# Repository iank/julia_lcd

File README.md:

# julia_lcd

TFT LCD panel, capacitive touch controller, Xilinx Cyclone IV FPGA, SDR SDRAM

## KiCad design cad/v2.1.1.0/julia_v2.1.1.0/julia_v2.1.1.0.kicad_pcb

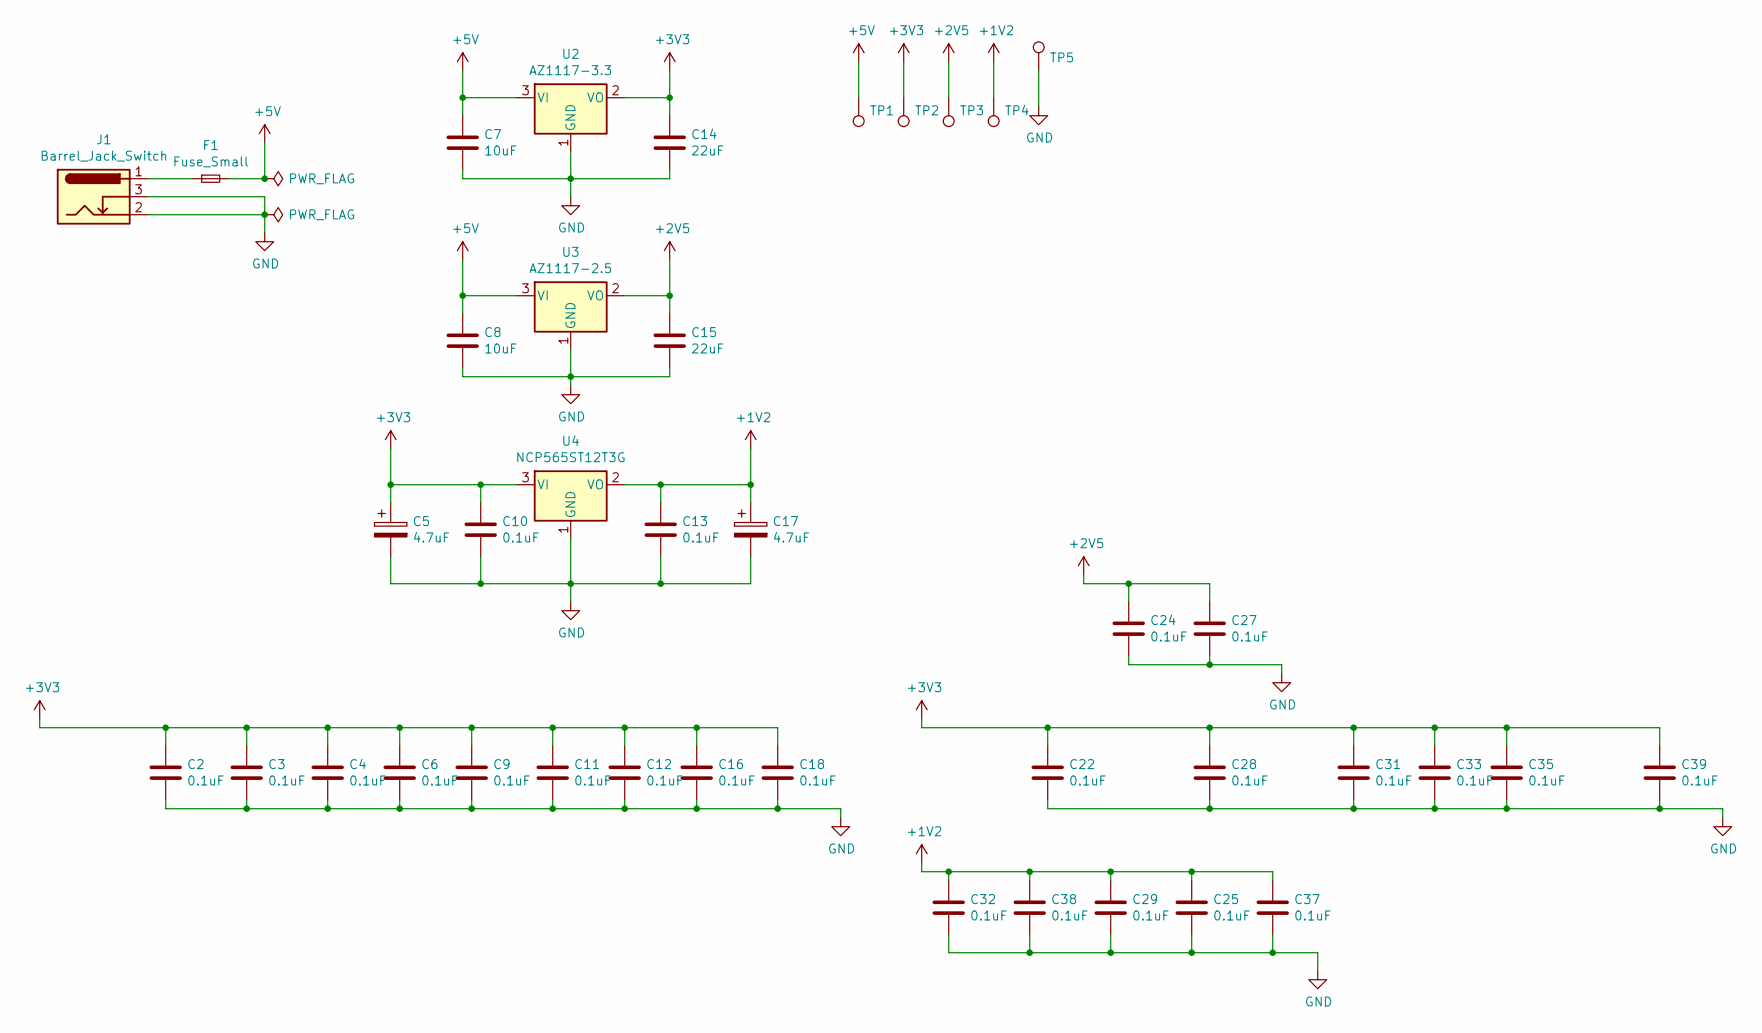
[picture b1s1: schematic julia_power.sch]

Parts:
C2, C3, C4, C6, C9, C10, C11, C12, C13, C16, C18, C22, C24, C25, C27, C28, C29, C31, C32, C33, C35, C37, C38, C39: 0.1uF; C_0402_1005Metric
C5, C17: 4.7uF; CP_EIA-2012-15_AVX-P
C7, C8: 10uF; C_0603_1608Metric
C14, C15: 22uF; C_0603_1608Metric
F1: Fuse_Small; Fuse_1206_3216Metric
J1: Barrel_Jack_Switch; BarrelJack_GCT_DCJ200-05-A-K1-A_SMD_Horizontal
TP1, TP2, TP3, TP4, TP5: TestPoint; TestPoint_THTPad_D1.0mm_Drill0.5mm
U2: AZ1117-3.3; SOT-223-3_TabPin2
U3: AZ1117-2.5; SOT-223-3_TabPin2
U4: NCP565ST12T3G; SOT-223-3_TabPin2

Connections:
+1V2: C13.1, C17.1, C25.1, C29.1, C32.1, C37.1, C38.1, TP4.1, U4.2 (VO); also elsewhere on the board
+2V5: C15.1, C24.1, C27.1, TP3.1, U3.2 (VO); also elsewhere on the board
+3V3: C2.1, C3.1, C4.1, C5.1, C6.1, C9.1, C10.1, C11.1, C12.1, C14.1, C16.1, C18.1, C22.1, C28.1, C31.1, C33.1, C35.1, C39.1, TP2.1, U2.2 (VO), U4.3 (VI); also elsewhere on the board
+5V: C7.1, C8.1, F1.2, TP1.1, U2.3 (VI), U3.3 (VI); also elsewhere on the board
GND: C2.2, C3.2, C4.2, C5.2, C6.2, C7.2, C8.2, C9.2, C10.2, C11.2, C12.2, C13.2, C14.2, C15.2, C16.2, C17.2, C18.2, C22.2, C24.2, C25.2, C27.2, C28.2, C29.2, C31.2, C32.2, C33.2, C35.2, C37.2, C38.2, C39.2, J1.2, J1.3, TP5.1, U2.1 (GND), U3.1 (GND), U4.1 (GND); also elsewhere on the board
unnamed: F1.1, J1.1

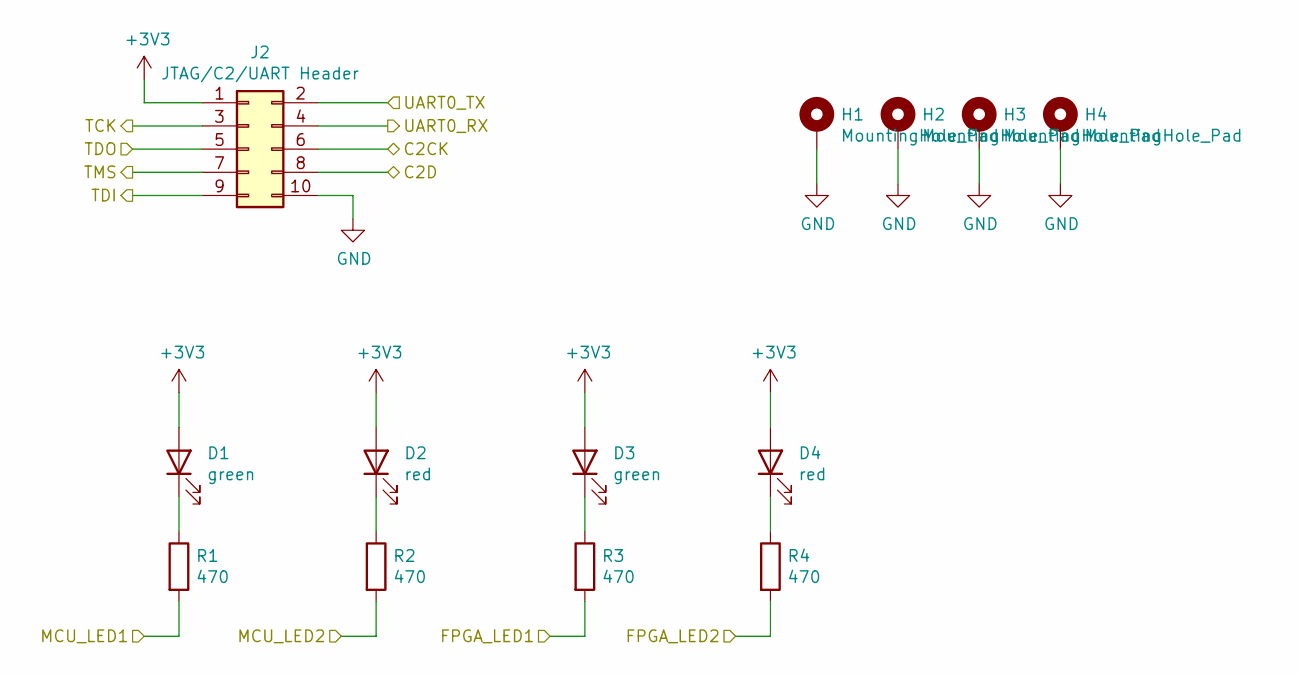
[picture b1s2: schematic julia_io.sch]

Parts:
D1, D3: green; LED_0603_1608Metric
D2, D4: red; LED_0603_1608Metric
H1, H2, H3, H4: MountingHole_Pad; MountingHole_2.2mm_M2_Pad
J2: JTAG/C2/UART Header; PinHeader_2x05_P1.27mm_Vertical
R1, R2, R3, R4: 470; R_0402_1005Metric

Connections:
+3V3: D1.2 (A), D2.2 (A), D3.2 (A), D4.2 (A), J2.1; also elsewhere on the board
/JuliaConfig/C2CK: J2.6; also elsewhere on the board
/JuliaConfig/C2D: J2.8; also elsewhere on the board
/JuliaConfig/MCU_LED1: R1.2; also elsewhere on the board
/JuliaConfig/MCU_LED2: R2.2; also elsewhere on the board
/JuliaConfig/UART0_RX: J2.4; also elsewhere on the board
/JuliaConfig/UART0_TX: J2.2; also elsewhere on the board
/JuliaFPGA/FPGA_LED1: R3.2; also elsewhere on the board
/JuliaFPGA/FPGA_LED2: R4.2; also elsewhere on the board
/JuliaFPGA/TCK: J2.3; also elsewhere on the board
/JuliaFPGA/TDI: J2.9; also elsewhere on the board
/JuliaFPGA/TDO: J2.5; also elsewhere on the board
/JuliaFPGA/TMS: J2.7; also elsewhere on the board
GND: H1.1, H2.1, H3.1, H4.1, J2.10; also elsewhere on the board
unnamed: D1.1 (K), R1.1
unnamed: D2.1 (K), R2.1
unnamed: D3.1 (K), R3.1
unnamed: D4.1 (K), R4.1

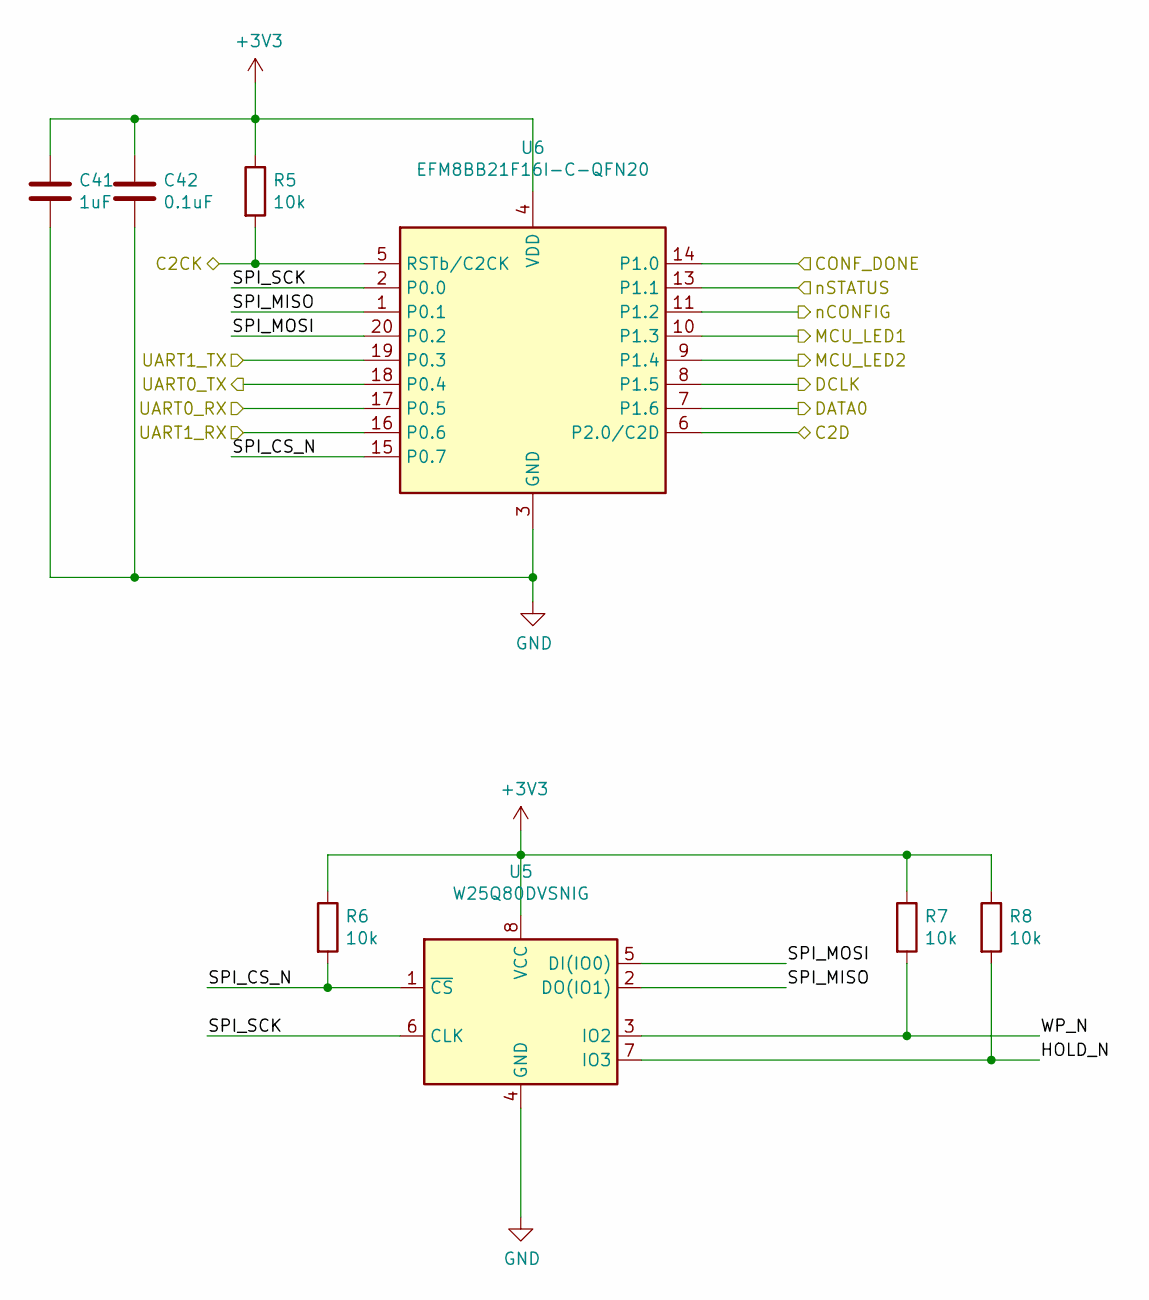
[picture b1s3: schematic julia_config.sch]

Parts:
C41: 1uF; C_0603_1608Metric
C42: 0.1uF; C_0402_1005Metric
R5, R6, R7, R8: 10k; R_0402_1005Metric
U5: W25Q80DVSNIG; SOIC-8_3.9x4.9mm_P1.27mm
U6: EFM8BB21F16I-C-QFN20; SiliconLabs_QFN-20-1EP_3x3mm_P0.5mm_EP1.8x1.8mm

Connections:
+3V3: C41.1, C42.1, R5.1, R6.1, R7.1, R8.1, U5.8 (VCC), U6.4 (VDD); also elsewhere on the board
/JuliaConfig/C2CK: R5.2, U6.5 (RSTb/C2CK); also elsewhere on the board
/JuliaConfig/C2D: U6.6 (P2.0/C2D); also elsewhere on the board
/JuliaConfig/CONF_DONE: U6.14 (P1.0); also elsewhere on the board
/JuliaConfig/DATA0: U6.7 (P1.6); also elsewhere on the board
/JuliaConfig/DCLK: U6.8 (P1.5); also elsewhere on the board
/JuliaConfig/HOLD_N: R8.2, U5.7 (IO3)
/JuliaConfig/MCU_LED1: U6.10 (P1.3); also elsewhere on the board
/JuliaConfig/MCU_LED2: U6.9 (P1.4); also elsewhere on the board
/JuliaConfig/SPI_CS_N: R6.2, U5.1 (~CS), U6.15 (P0.7)
/JuliaConfig/SPI_MISO: U5.2 (DO(IO1)), U6.1 (P0.1)
/JuliaConfig/SPI_MOSI: U5.5 (DI(IO0)), U6.20 (P0.2)
/JuliaConfig/SPI_SCK: U5.6 (CLK), U6.2 (P0.0)
/JuliaConfig/UART0_RX: U6.17 (P0.5); also elsewhere on the board
/JuliaConfig/UART0_TX: U6.18 (P0.4); also elsewhere on the board
/JuliaConfig/UART1_RX: U6.16 (P0.6); also elsewhere on the board
/JuliaConfig/UART1_TX: U6.19 (P0.3); also elsewhere on the board
/JuliaConfig/WP_N: R7.2, U5.3 (IO2)
/JuliaConfig/nCONFIG: U6.11 (P1.2); also elsewhere on the board
/JuliaConfig/nSTATUS: U6.13 (P1.1); also elsewhere on the board
GND: C41.2, C42.2, U5.4 (GND), U6.3 (GND), U6.12 (GND), U6.21 (GND); also elsewhere on the board

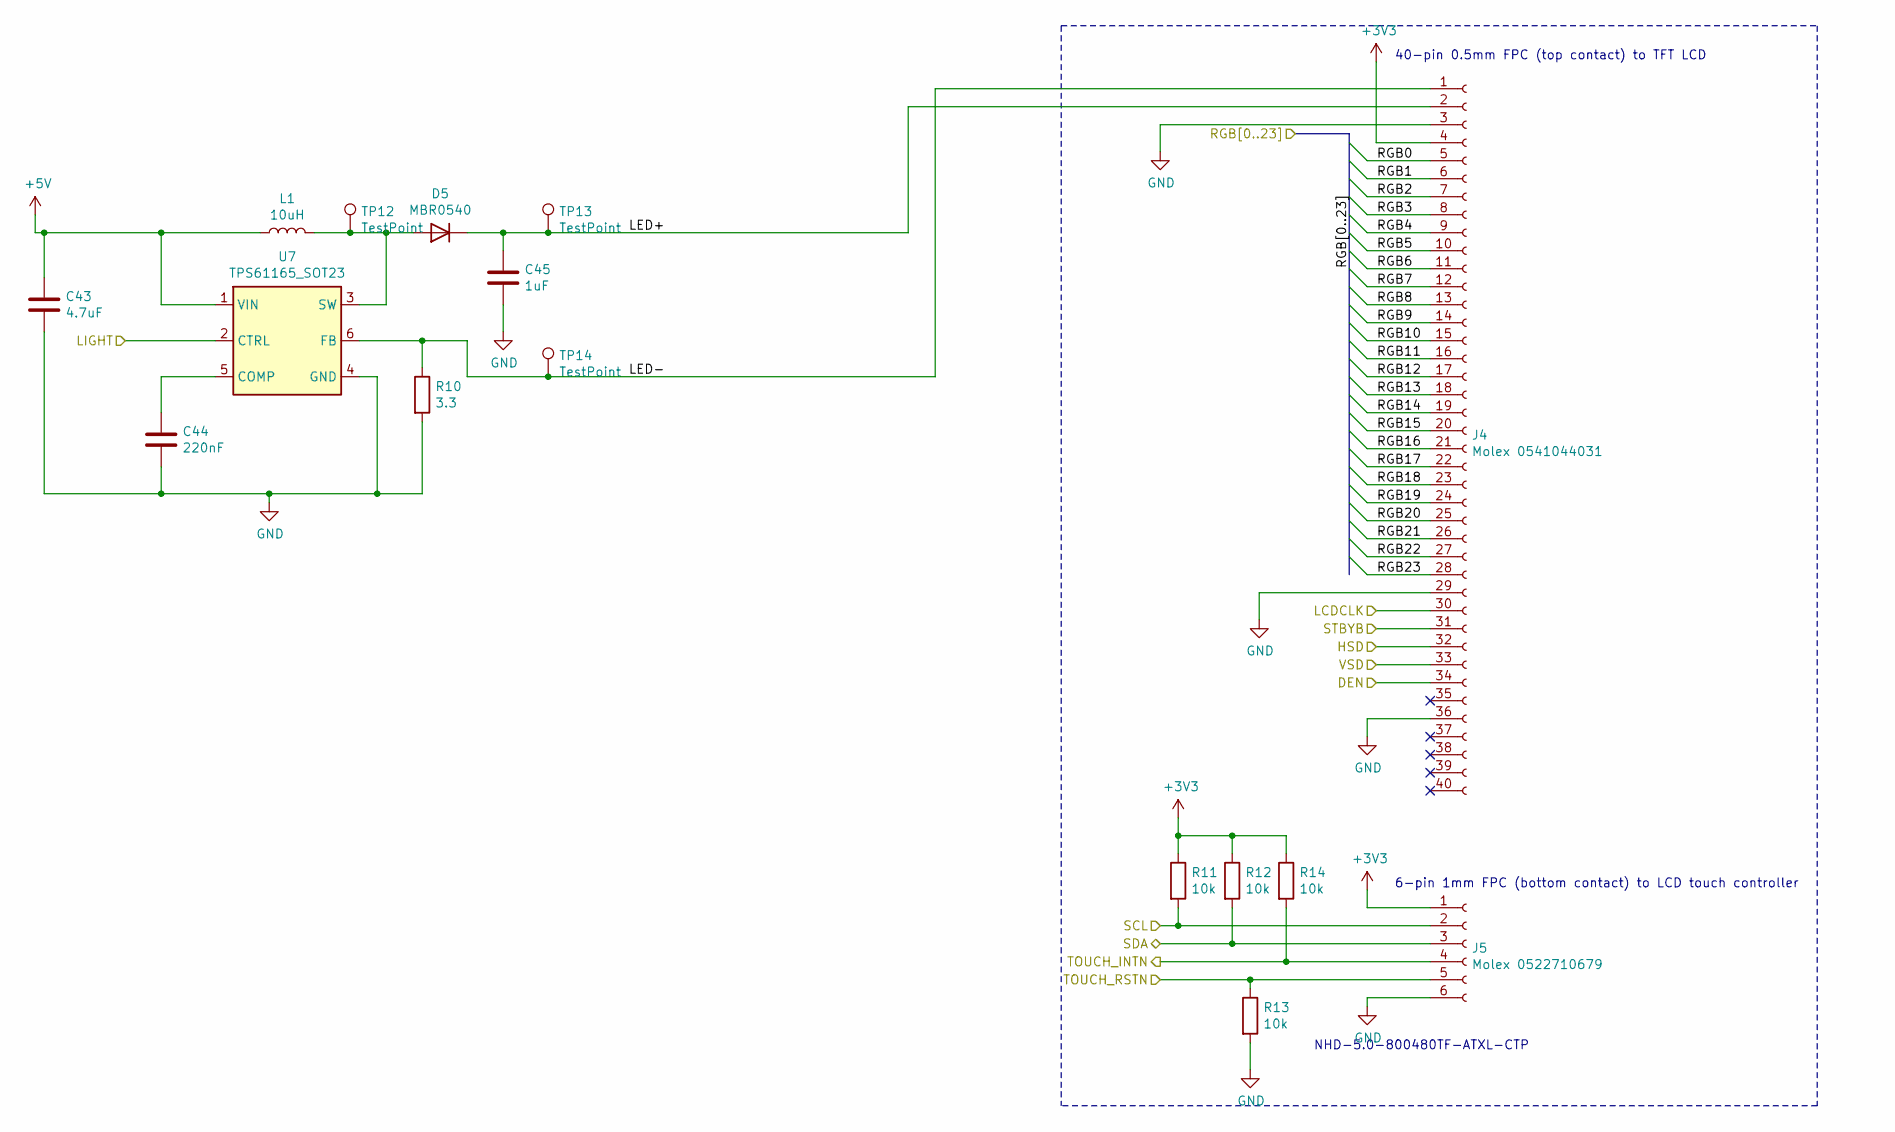
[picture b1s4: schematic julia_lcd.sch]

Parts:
C43: 4.7uF; C_0603_1608Metric
C44: 220nF; C_0402_1005Metric
C45: 1uF; C_0603_1608Metric
D5: MBR0540; D_SOD-123
J4: Molex 0541044031; Molex_54104-4031_1x40-P0.5mm_Horizontal
J5: Molex 0522710679; Molex_52271-0679_1x06-1MP_P1.00mm_Horizontal
L1: 10uH; Murata_D53LC_A915AY-100M
R10: 3.3; R_0805_2012Metric
R11, R12, R13, R14: 10k; R_0402_1005Metric
TP12, TP13, TP14: TestPoint; TestPoint_THTPad_D1.0mm_Drill0.5mm
U7: TPS61165_SOT23; SOT-23-6

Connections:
+3V3: J4.4, J5.1, R11.1, R12.1, R14.1; also elsewhere on the board
+5V: C43.1, L1.1, U7.1 (VIN); also elsewhere on the board
/JuliaFPGA/DEN: J4.34; also elsewhere on the board
/JuliaFPGA/HSD: J4.32; also elsewhere on the board
/JuliaFPGA/LCDCLK: J4.30; also elsewhere on the board
/JuliaFPGA/LIGHT: U7.2 (CTRL); also elsewhere on the board
/JuliaFPGA/RGB0: J4.5; also elsewhere on the board
/JuliaFPGA/RGB1: J4.6; also elsewhere on the board
/JuliaFPGA/RGB2: J4.7; also elsewhere on the board
/JuliaFPGA/RGB3: J4.8; also elsewhere on the board
/JuliaFPGA/RGB4: J4.9; also elsewhere on the board
/JuliaFPGA/RGB5: J4.10; also elsewhere on the board
/JuliaFPGA/RGB6: J4.11; also elsewhere on the board
/JuliaFPGA/RGB7: J4.12; also elsewhere on the board
/JuliaFPGA/RGB8: J4.13; also elsewhere on the board
/JuliaFPGA/RGB9: J4.14; also elsewhere on the board
/JuliaFPGA/RGB10: J4.15; also elsewhere on the board
/JuliaFPGA/RGB11: J4.16; also elsewhere on the board
/JuliaFPGA/RGB12: J4.17; also elsewhere on the board
/JuliaFPGA/RGB13: J4.18; also elsewhere on the board
/JuliaFPGA/RGB14: J4.19; also elsewhere on the board
/JuliaFPGA/RGB15: J4.20; also elsewhere on the board
/JuliaFPGA/RGB16: J4.21; also elsewhere on the board
/JuliaFPGA/RGB17: J4.22; also elsewhere on the board
/JuliaFPGA/RGB18: J4.23; also elsewhere on the board
/JuliaFPGA/RGB19: J4.24; also elsewhere on the board
/JuliaFPGA/RGB20: J4.25; also elsewhere on the board
/JuliaFPGA/RGB21: J4.26; also elsewhere on the board
/JuliaFPGA/RGB22: J4.27; also elsewhere on the board
/JuliaFPGA/RGB23: J4.28; also elsewhere on the board
/JuliaFPGA/SCL: J5.2, R11.2; also elsewhere on the board
/JuliaFPGA/SDA: J5.3, R12.2; also elsewhere on the board
/JuliaFPGA/STBYB: J4.31; also elsewhere on the board
/JuliaFPGA/TOUCH_INTN: J5.4, R14.2; also elsewhere on the board
/JuliaFPGA/TOUCH_RSTN: J5.5, R13.1; also elsewhere on the board
/JuliaFPGA/VSD: J4.33; also elsewhere on the board
/JuliaLCD/LED+: C45.1, D5.1 (K), J4.2, TP13.1
/JuliaLCD/LED-: J4.1, R10.1, TP14.1, U7.6 (FB)
GND: C43.2, C44.2, C45.2, J4.3, J4.29, J4.36, J5.6, R10.2, R13.2, U7.4 (GND); also elsewhere on the board
unnamed: C44.1, U7.5 (COMP)
unnamed: D5.2 (A), L1.2, TP12.1, U7.3 (SW)

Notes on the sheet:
40-pin 0.5mm FPC (top contact) to TFT LCD
NHD-5.0-800480TF-ATXL-CTP
6-pin 1mm FPC (bottom contact) to LCD touch controller

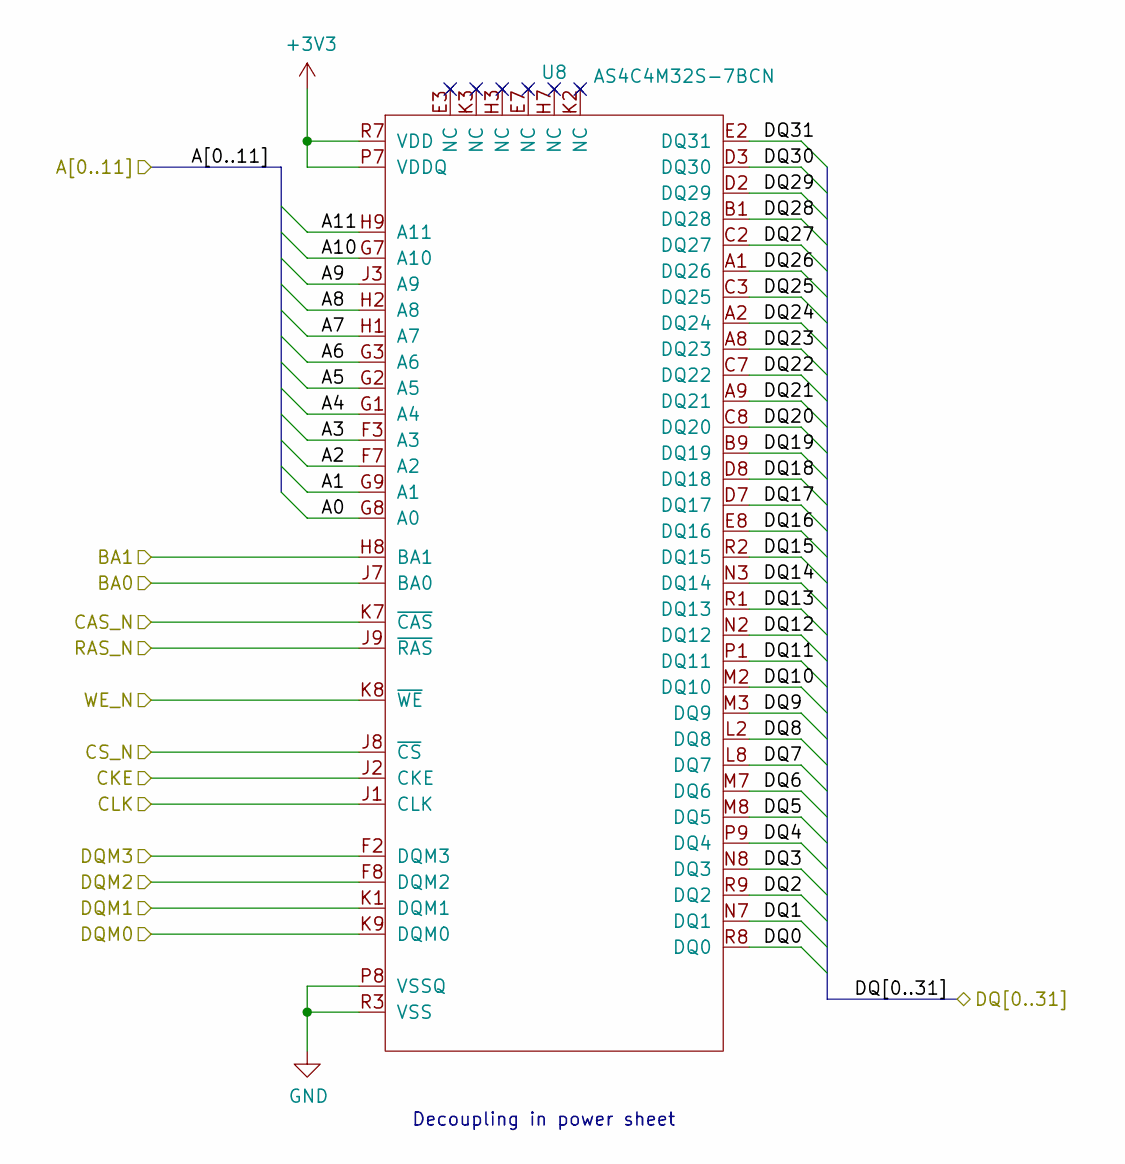
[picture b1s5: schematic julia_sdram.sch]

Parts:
U8: AS4C4M32S-7BCN

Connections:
+3V3: U8.A7 (VDD), U8.B2 (VDDQ), U8.B7 (VDDQ), U8.C9 (VDDQ), U8.D9 (VDDQ), U8.E1 (VDDQ), U8.F9 (VDD), U8.L1 (VDDQ), U8.L7 (VDD), U8.M9 (VDDQ), U8.N9 (VDDQ), U8.P2 (VDDQ), U8.P7 (VDDQ), U8.R7 (VDD); also elsewhere on the board
/JuliaFPGA/A0: U8.G8 (A0); also elsewhere on the board
/JuliaFPGA/A1: U8.G9 (A1); also elsewhere on the board
/JuliaFPGA/A2: U8.F7 (A2); also elsewhere on the board
/JuliaFPGA/A3: U8.F3 (A3); also elsewhere on the board
/JuliaFPGA/A4: U8.G1 (A4); also elsewhere on the board
/JuliaFPGA/A5: U8.G2 (A5); also elsewhere on the board
/JuliaFPGA/A6: U8.G3 (A6); also elsewhere on the board
/JuliaFPGA/A7: U8.H1 (A7); also elsewhere on the board
/JuliaFPGA/A8: U8.H2 (A8); also elsewhere on the board
/JuliaFPGA/A9: U8.J3 (A9); also elsewhere on the board
/JuliaFPGA/A10: U8.G7 (A10); also elsewhere on the board
/JuliaFPGA/A11: U8.H9 (A11); also elsewhere on the board
/JuliaFPGA/BA0: U8.J7 (BA0); also elsewhere on the board
/JuliaFPGA/BA1: U8.H8 (BA1); also elsewhere on the board
/JuliaFPGA/CAS_N: U8.K7 (~CAS~); also elsewhere on the board
/JuliaFPGA/DQ0: U8.R8 (DQ0); also elsewhere on the board
/JuliaFPGA/DQ1: U8.N7 (DQ1); also elsewhere on the board
/JuliaFPGA/DQ2: U8.R9 (DQ2); also elsewhere on the board
/JuliaFPGA/DQ3: U8.N8 (DQ3); also elsewhere on the board
/JuliaFPGA/DQ4: U8.P9 (DQ4); also elsewhere on the board
/JuliaFPGA/DQ5: U8.M8 (DQ5); also elsewhere on the board
/JuliaFPGA/DQ6: U8.M7 (DQ6); also elsewhere on the board
/JuliaFPGA/DQ7: U8.L8 (DQ7); also elsewhere on the board
/JuliaFPGA/DQ8: U8.L2 (DQ8); also elsewhere on the board
/JuliaFPGA/DQ9: U8.M3 (DQ9); also elsewhere on the board
/JuliaFPGA/DQ10: U8.M2 (DQ10); also elsewhere on the board
/JuliaFPGA/DQ11: U8.P1 (DQ11); also elsewhere on the board
/JuliaFPGA/DQ12: U8.N2 (DQ12); also elsewhere on the board
/JuliaFPGA/DQ13: U8.R1 (DQ13); also elsewhere on the board
/JuliaFPGA/DQ14: U8.N3 (DQ14); also elsewhere on the board
/JuliaFPGA/DQ15: U8.R2 (DQ15); also elsewhere on the board
/JuliaFPGA/DQ16: U8.E8 (DQ16); also elsewhere on the board
/JuliaFPGA/DQ17: U8.D7 (DQ17); also elsewhere on the board
/JuliaFPGA/DQ18: U8.D8 (DQ18); also elsewhere on the board
/JuliaFPGA/DQ19: U8.B9 (DQ19); also elsewhere on the board
/JuliaFPGA/DQ20: U8.C8 (DQ20); also elsewhere on the board
/JuliaFPGA/DQ21: U8.A9 (DQ21); also elsewhere on the board
/JuliaFPGA/DQ22: U8.C7 (DQ22); also elsewhere on the board
/JuliaFPGA/DQ23: U8.A8 (DQ23); also elsewhere on the board
/JuliaFPGA/DQ24: U8.A2 (DQ24); also elsewhere on the board
/JuliaFPGA/DQ25: U8.C3 (DQ25); also elsewhere on the board
/JuliaFPGA/DQ26: U8.A1 (DQ26); also elsewhere on the board
/JuliaFPGA/DQ27: U8.C2 (DQ27); also elsewhere on the board
/JuliaFPGA/DQ28: U8.B1 (DQ28); also elsewhere on the board
/JuliaFPGA/DQ29: U8.D2 (DQ29); also elsewhere on the board
/JuliaFPGA/DQ30: U8.D3 (DQ30); also elsewhere on the board
/JuliaFPGA/DQ31: U8.E2 (DQ31); also elsewhere on the board
/JuliaFPGA/DQM0: U8.K9 (DQM0); also elsewhere on the board
/JuliaFPGA/DQM1: U8.K1 (DQM1); also elsewhere on the board
/JuliaFPGA/DQM2: U8.F8 (DQM2); also elsewhere on the board
/JuliaFPGA/DQM3: U8.F2 (DQM3); also elsewhere on the board
/JuliaFPGA/RAS_N: U8.J9 (~RAS~); also elsewhere on the board
/JuliaFPGA/SDRAM_WE_N: U8.K8 (~WE~); also elsewhere on the board
/JuliaSDRAM/CKE: U8.J2 (CKE); also elsewhere on the board
/JuliaSDRAM/CLK: U8.J1 (CLK); also elsewhere on the board
/JuliaSDRAM/CS_N: U8.J8 (~CS~); also elsewhere on the board
GND: U8.A3 (VSS), U8.B3 (VSSQ), U8.B8 (VSSQ), U8.C1 (VSSQ), U8.D1 (VSSQ), U8.E9 (VSSQ), U8.F1 (VSS), U8.L3 (VSS), U8.L9 (VSSQ), U8.M1 (VSSQ), U8.N1 (VSSQ), U8.P3 (VSSQ), U8.P8 (VSSQ), U8.R3 (VSS); also elsewhere on the board

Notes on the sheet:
Decoupling in power sheet

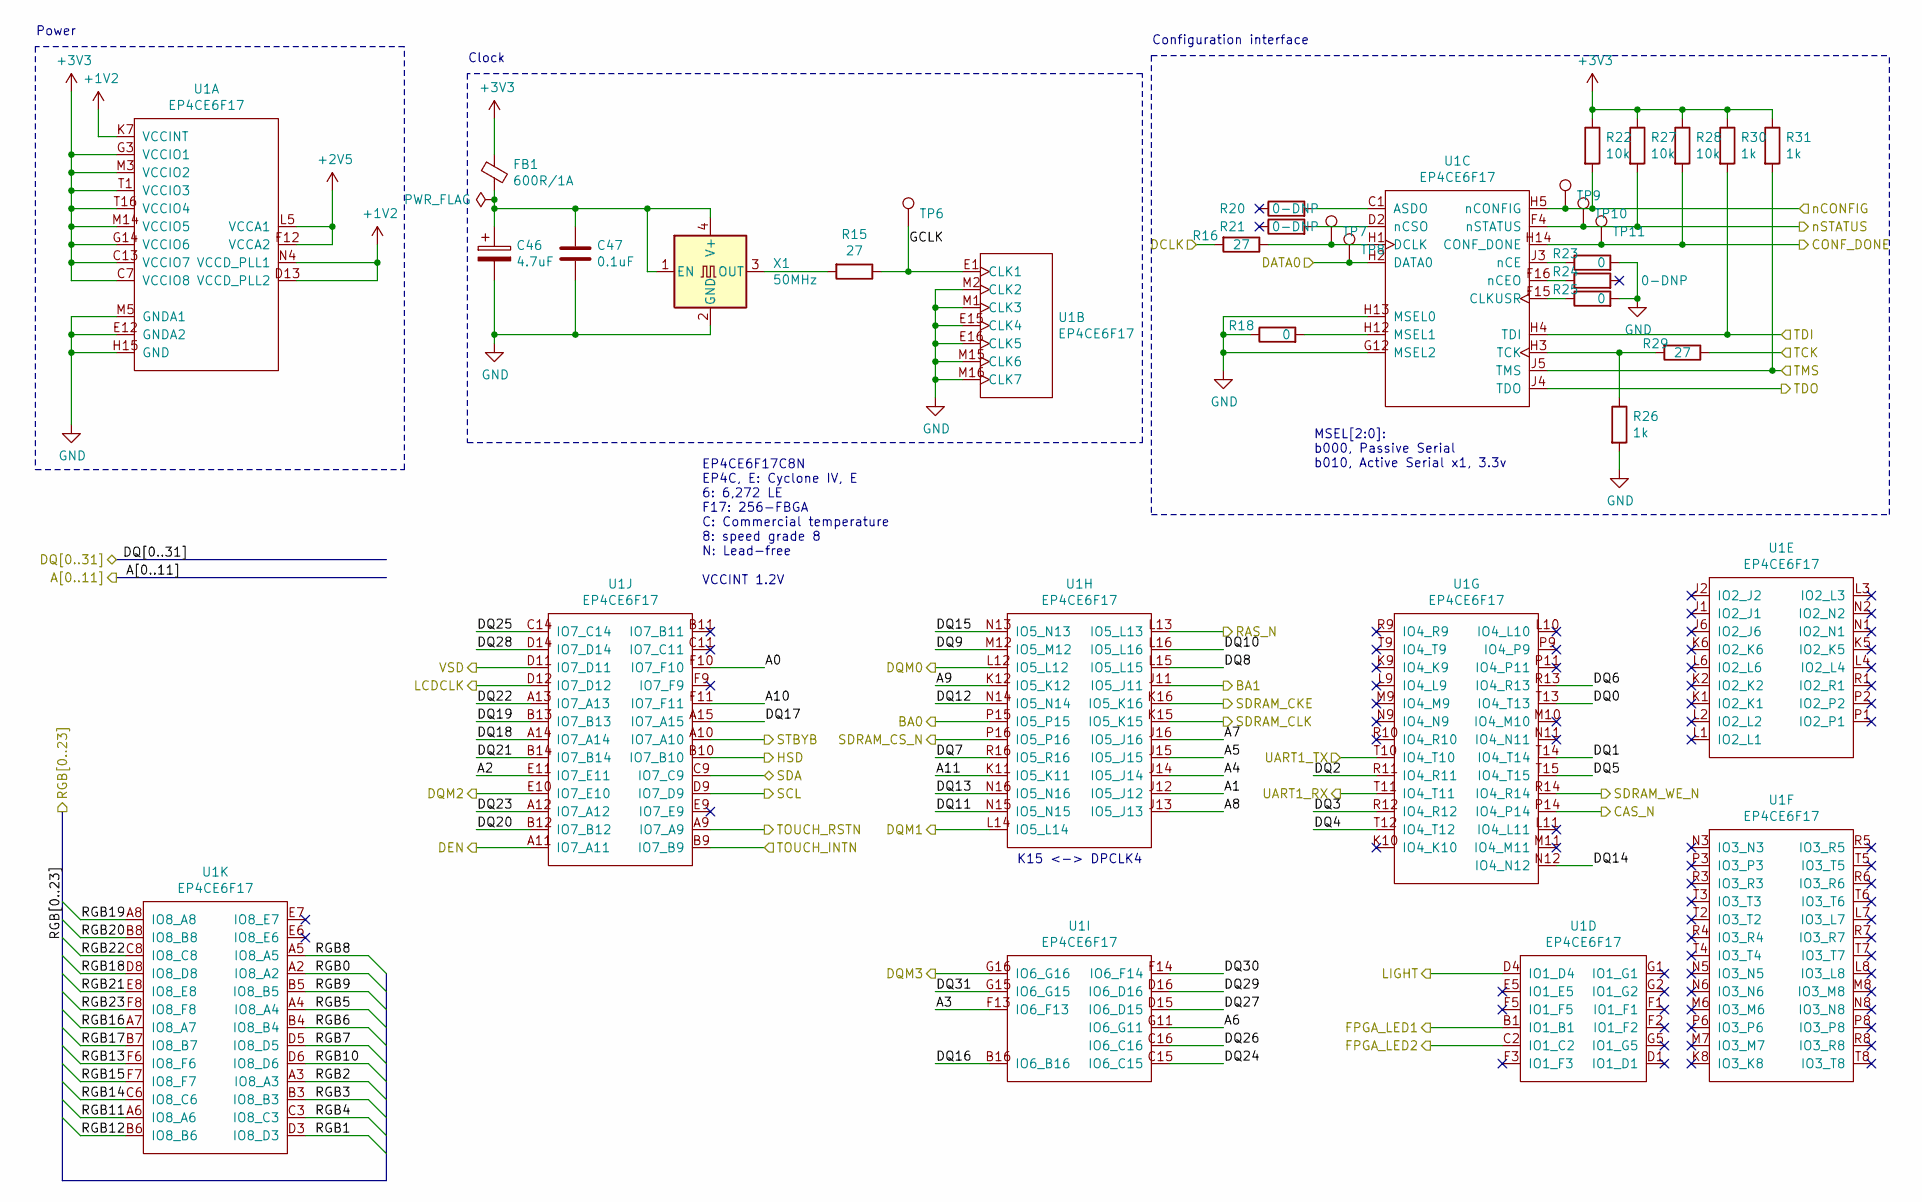
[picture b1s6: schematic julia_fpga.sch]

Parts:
C46: 4.7uF; CP_EIA-2012-15_AVX-P
C47: 0.1uF; C_0402_1005Metric
FB1: 600R/1A; L_0603_1608Metric
R15, R16, R29: 27; R_0402_1005Metric
R18, R23, R25: 0; R_0402_1005Metric
R20, R21, R24: 0-DNP; R_0402_1005Metric
R22, R27, R28: 10k; R_0402_1005Metric
R26, R30, R31: 1k; R_0402_1005Metric
TP6, TP7, TP8, TP9, TP10, TP11: TestPoint; TestPoint_THTPad_D1.0mm_Drill0.5mm
U1: EP4CE6F17; BGA-256_17.0x17.0mm_Layout16x16_P1.0mm_Ball0.5mm_Pad0.4mm_N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
X1: 50MHz; Oscillator_SMD_EuroQuartz_XO91-4Pin_7.0x5.0mm

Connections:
+1V2: U1.D13 (VCCD_PLL2), U1.G6 (VCCINT), U1.G7 (VCCINT), U1.G8 (VCCINT), U1.G9 (VCCINT), U1.G10 (VCCINT), U1.H6 (VCCINT), U1.H11 (VCCINT), U1.K7 (VCCINT), U1.N4 (VCCD_PLL1); also elsewhere on the board
+2V5: U1.F12 (VCCA2), U1.L5 (VCCA1); also elsewhere on the board
+3V3: FB1.1, R22.1, R27.1, R28.1, R30.1, R31.1, U1.A1 (VCCIO8), U1.A16 (VCCIO7), U1.C4 (VCCIO8), U1.C7 (VCCIO8), U1.C10 (VCCIO7), U1.C13 (VCCIO7), U1.E3 (VCCIO1), U1.E14 (VCCIO6), U1.G3 (VCCIO1), U1.G14 (VCCIO6), U1.K3 (VCCIO2), U1.K14 (VCCIO5), U1.M3 (VCCIO2), U1.M14 (VCCIO5), U1.P4 (VCCIO3), U1.P7 (VCCIO3), U1.P10 (VCCIO4), U1.P13 (VCCIO4), U1.T1 (VCCIO3), U1.T16 (VCCIO4); also elsewhere on the board
/JuliaConfig/CONF_DONE: R28.2, TP11.1, U1.H14 (CONF_DONE); also elsewhere on the board
/JuliaConfig/DATA0: TP8.1, U1.H2 (DATA0); also elsewhere on the board
/JuliaConfig/DCLK: R16.2; also elsewhere on the board
/JuliaConfig/UART1_RX: U1.T11 (IO4_T11); also elsewhere on the board
/JuliaConfig/UART1_TX: U1.T10 (IO4_T10); also elsewhere on the board
/JuliaConfig/nCONFIG: R22.2, TP9.1, U1.H5 (nCONFIG); also elsewhere on the board
/JuliaConfig/nSTATUS: R27.2, TP10.1, U1.F4 (nSTATUS); also elsewhere on the board
/JuliaFPGA/A0: U1.F10 (IO7_F10); also elsewhere on the board
/JuliaFPGA/A1: U1.J12 (IO5_J12); also elsewhere on the board
/JuliaFPGA/A2: U1.E11 (IO7_E11); also elsewhere on the board
/JuliaFPGA/A3: U1.F13 (IO6_F13); also elsewhere on the board
/JuliaFPGA/A4: U1.J14 (IO5_J14); also elsewhere on the board
/JuliaFPGA/A5: U1.J15 (IO5_J15); also elsewhere on the board
/JuliaFPGA/A6: U1.G11 (IO6_G11); also elsewhere on the board
/JuliaFPGA/A7: U1.J16 (IO5_J16); also elsewhere on the board
/JuliaFPGA/A8: U1.J13 (IO5_J13); also elsewhere on the board
/JuliaFPGA/A9: U1.K12 (IO5_K12); also elsewhere on the board
/JuliaFPGA/A10: U1.F11 (IO7_F11); also elsewhere on the board
/JuliaFPGA/A11: U1.K11 (IO5_K11); also elsewhere on the board
/JuliaFPGA/BA0: U1.P15 (IO5_P15); also elsewhere on the board
/JuliaFPGA/BA1: U1.J11 (IO5_J11); also elsewhere on the board
/JuliaFPGA/CAS_N: U1.P14 (IO4_P14); also elsewhere on the board
/JuliaFPGA/DEN: U1.A11 (IO7_A11); also elsewhere on the board
/JuliaFPGA/DQ0: U1.T13 (IO4_T13); also elsewhere on the board
/JuliaFPGA/DQ1: U1.T14 (IO4_T14); also elsewhere on the board
/JuliaFPGA/DQ2: U1.R11 (IO4_R11); also elsewhere on the board
/JuliaFPGA/DQ3: U1.R12 (IO4_R12); also elsewhere on the board
/JuliaFPGA/DQ4: U1.T12 (IO4_T12); also elsewhere on the board
/JuliaFPGA/DQ5: U1.T15 (IO4_T15); also elsewhere on the board
/JuliaFPGA/DQ6: U1.R13 (IO4_R13); also elsewhere on the board
/JuliaFPGA/DQ7: U1.R16 (IO5_R16); also elsewhere on the board
/JuliaFPGA/DQ8: U1.L15 (IO5_L15); also elsewhere on the board
/JuliaFPGA/DQ9: U1.M12 (IO5_M12); also elsewhere on the board
/JuliaFPGA/DQ10: U1.L16 (IO5_L16); also elsewhere on the board
/JuliaFPGA/DQ11: U1.N15 (IO5_N15); also elsewhere on the board
/JuliaFPGA/DQ12: U1.N14 (IO5_N14); also elsewhere on the board
/JuliaFPGA/DQ13: U1.N16 (IO5_N16); also elsewhere on the board
/JuliaFPGA/DQ14: U1.N12 (IO4_N12); also elsewhere on the board
/JuliaFPGA/DQ15: U1.N13 (IO5_N13); also elsewhere on the board
/JuliaFPGA/DQ16: U1.B16 (IO6_B16); also elsewhere on the board
/JuliaFPGA/DQ17: U1.A15 (IO7_A15); also elsewhere on the board
/JuliaFPGA/DQ18: U1.A14 (IO7_A14); also elsewhere on the board
/JuliaFPGA/DQ19: U1.B13 (IO7_B13); also elsewhere on the board
/JuliaFPGA/DQ20: U1.B12 (IO7_B12); also elsewhere on the board
/JuliaFPGA/DQ21: U1.B14 (IO7_B14); also elsewhere on the board
/JuliaFPGA/DQ22: U1.A13 (IO7_A13); also elsewhere on the board
/JuliaFPGA/DQ23: U1.A12 (IO7_A12); also elsewhere on the board
/JuliaFPGA/DQ24: U1.C15 (IO6_C15); also elsewhere on the board
/JuliaFPGA/DQ25: U1.C14 (IO7_C14); also elsewhere on the board
/JuliaFPGA/DQ26: U1.C16 (IO6_C16); also elsewhere on the board
/JuliaFPGA/DQ27: U1.D15 (IO6_D15); also elsewhere on the board
/JuliaFPGA/DQ28: U1.D14 (IO7_D14); also elsewhere on the board
/JuliaFPGA/DQ29: U1.D16 (IO6_D16); also elsewhere on the board
/JuliaFPGA/DQ30: U1.F14 (IO6_F14); also elsewhere on the board
/JuliaFPGA/DQ31: U1.G15 (IO6_G15); also elsewhere on the board
/JuliaFPGA/DQM0: U1.L12 (IO5_L12); also elsewhere on the board
/JuliaFPGA/DQM1: U1.L14 (IO5_L14); also elsewhere on the board
/JuliaFPGA/DQM2: U1.E10 (IO7_E10); also elsewhere on the board
/JuliaFPGA/DQM3: U1.G16 (IO6_G16); also elsewhere on the board
/JuliaFPGA/FPGA_LED1: U1.B1 (IO1_B1); also elsewhere on the board
/JuliaFPGA/FPGA_LED2: U1.C2 (IO1_C2); also elsewhere on the board
/JuliaFPGA/GCLK: R15.1, TP6.1, U1.E1 (CLK1)
/JuliaFPGA/HSD: U1.B10 (IO7_B10); also elsewhere on the board
/JuliaFPGA/LCDCLK: U1.D12 (IO7_D12); also elsewhere on the board
/JuliaFPGA/LIGHT: U1.D4 (IO1_D4); also elsewhere on the board
/JuliaFPGA/RAS_N: U1.L13 (IO5_L13); also elsewhere on the board
/JuliaFPGA/RGB0: U1.A2 (IO8_A2); also elsewhere on the board
/JuliaFPGA/RGB1: U1.D3 (IO8_D3); also elsewhere on the board
/JuliaFPGA/RGB2: U1.A3 (IO8_A3); also elsewhere on the board
/JuliaFPGA/RGB3: U1.B3 (IO8_B3); also elsewhere on the board
/JuliaFPGA/RGB4: U1.C3 (IO8_C3); also elsewhere on the board
/JuliaFPGA/RGB5: U1.A4 (IO8_A4); also elsewhere on the board
/JuliaFPGA/RGB6: U1.B4 (IO8_B4); also elsewhere on the board
/JuliaFPGA/RGB7: U1.D5 (IO8_D5); also elsewhere on the board
/JuliaFPGA/RGB8: U1.A5 (IO8_A5); also elsewhere on the board
/JuliaFPGA/RGB9: U1.B5 (IO8_B5); also elsewhere on the board
/JuliaFPGA/RGB10: U1.D6 (IO8_D6); also elsewhere on the board
/JuliaFPGA/RGB11: U1.A6 (IO8_A6); also elsewhere on the board
/JuliaFPGA/RGB12: U1.B6 (IO8_B6); also elsewhere on the board
/JuliaFPGA/RGB13: U1.F6 (IO8_F6); also elsewhere on the board
/JuliaFPGA/RGB14: U1.C6 (IO8_C6); also elsewhere on the board
/JuliaFPGA/RGB15: U1.F7 (IO8_F7); also elsewhere on the board
/JuliaFPGA/RGB16: U1.A7 (IO8_A7); also elsewhere on the board
/JuliaFPGA/RGB17: U1.B7 (IO8_B7); also elsewhere on the board
/JuliaFPGA/RGB18: U1.D8 (IO8_D8); also elsewhere on the board
/JuliaFPGA/RGB19: U1.A8 (IO8_A8); also elsewhere on the board
/JuliaFPGA/RGB20: U1.B8 (IO8_B8); also elsewhere on the board
/JuliaFPGA/RGB21: U1.E8 (IO8_E8); also elsewhere on the board
/JuliaFPGA/RGB22: U1.C8 (IO8_C8); also elsewhere on the board
/JuliaFPGA/RGB23: U1.F8 (IO8_F8); also elsewhere on the board
/JuliaFPGA/SCL: U1.D9 (IO7_D9); also elsewhere on the board
/JuliaFPGA/SDA: U1.C9 (IO7_C9); also elsewhere on the board
/JuliaFPGA/SDRAM_WE_N: U1.R14 (IO4_R14); also elsewhere on the board
/JuliaFPGA/STBYB: U1.A10 (IO7_A10); also elsewhere on the board
/JuliaFPGA/TCK: R29.1; also elsewhere on the board
/JuliaFPGA/TDI: R30.2, U1.H4 (TDI); also elsewhere on the board
/JuliaFPGA/TDO: U1.J4 (TDO); also elsewhere on the board
/JuliaFPGA/TMS: R31.2, U1.J5 (TMS); also elsewhere on the board
/JuliaFPGA/TOUCH_INTN: U1.B9 (IO7_B9); also elsewhere on the board
/JuliaFPGA/TOUCH_RSTN: U1.A9 (IO7_A9); also elsewhere on the board
/JuliaFPGA/VSD: U1.D11 (IO7_D11); also elsewhere on the board
/JuliaSDRAM/CKE: U1.K16 (IO5_K16); also elsewhere on the board
/JuliaSDRAM/CLK: U1.K15 (IO5_K15); also elsewhere on the board
/JuliaSDRAM/CS_N: U1.P16 (IO5_P16); also elsewhere on the board
GND: C46.2, C47.2, R18.1, R23.2, R25.2, R26.2, U1.B2 (GND), U1.B15 (GND), U1.C5 (GND), U1.C12 (GND), U1.D7 (GND), U1.D10 (GND), U1.E2 (GND), U1.E4 (GND), U1.E12 (GNDA2), U1.E13 (GND), U1.E15 (CLK4), U1.E16 (CLK5), U1.G4 (GND), U1.G12 (MSEL2), U1.G13 (GND), U1.H7 (GND), U1.H8 (GND), U1.H9 (GND), U1.H10 (GND), U1.H13 (MSEL0), U1.H15 (GND), U1.H16 (GND), U1.J7 (GND), U1.J8 (GND), U1.J9 (GND), U1.J10 (GND), U1.K4 (GND), U1.K13 (GND), U1.M1 (CLK3), U1.M2 (CLK2), U1.M4 (GND), U1.M5 (GNDA1), U1.M13 (GND), U1.M15 (CLK6), U1.M16 (CLK7), U1.N7 (GND), U1.N10 (GND), U1.P5 (GND), U1.P12 (GND), U1.R2 (GND), U1.R15 (GND), X1.2 (GND); also elsewhere on the board
unnamed: C46.1, C47.1, FB1.2, X1.1 (EN), X1.4 (V+)
unnamed: R15.2, X1.3 (OUT)
unnamed: R16.1, TP7.1, U1.H1 (DCLK)
unnamed: R18.2, U1.H12 (MSEL1)
unnamed: R20.2, U1.C1 (ASDO)
unnamed: R21.2, U1.D2 (nCSO)
unnamed: R23.1, U1.J3 (nCE)
unnamed: R24.1, U1.F16 (nCEO)
unnamed: R25.1, U1.F15 (CLKUSR)
unnamed: R26.1, R29.2, U1.H3 (TCK)

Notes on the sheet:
EP4CE6F17C8N EP4C, E: Cyclone IV, E 6: 6,272 LE F17: 256-FBGA C: Commercial temperature 8: speed grade 8 N: Lead-free VCCINT 1.2V
MSEL[2:0]: b000, Passive Serial b010, Active Serial x1, 3.3v
Power
Clock
Configuration interface
K15 <-> DPCLK4

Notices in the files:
src/fpga/julia.qsf:
Copyright (C) 2020  Intel Corporation. All rights reserved.
parts and their libraries:
Copyright 2016 Accelerated Designs. All rights reserved.
